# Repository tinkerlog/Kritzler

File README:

==============
 Der Kritzler
==============

 Der Kritzler is a software and hardware platform for developing wall plotters. 
 It consists of a set of Processing sketches (see src/ folder), Arduino firmware 
 (firmware/ folder) and some electronics (some files in the design/ folder). 

 More can be found here:
 http://tinkerlog.com/2011/09/02/der-kritzler/
 
 If you want me to pull your changes, please consider:
 * Use spaces, no tabs.
 * Indention: 2 spaces.

 src/ 
      Contains Processing/Java sources, ready to use in Eclipse.
      Take a look at http://processing.org/learning/eclipse/
      to see how to set things up.
      
 firmware/
      Contains Arduino firmware for the Kritzler.

 jpg_to_svg_bw.sh
      Script to convert a bitmap into an SVG.
      Needs imagemagick and potrace.
    
 jpg_to_svg.sh
      Starts the processing sketch to make a jittered SVG
      out of a bitmap (JPG).
      
 fill_svg.sh 
      Starts the processing sketch to fill SVG outlines with
      with diagonal lines.
      
 plotter.sh
      Starts the processing sketch that sends SVGs to the Kritzler.

===========
 Changelog
===========
 + Added controlP5 menus and buttons to the Plotter UI.
 + Added real-time pen location tracking - Jason Webb (5/25/2012)
 + Added Javadoc comments and consistent formatting added by - Jason Webb (5/25/2012)
 + Added ability to navigate through all SVG files in BUFFER_ACC folder using [ (back) and ] (forward) - Jason Webb (5/31/2012)
 + Added toggle-able grid to canvas, for accurate positioning (toggle with 'g') - Jason Webb (6/1/2012)
 + Added toggle-able bounding box for SVG shape, with centroid markings, for accurate positioning (toggle with 'b') - Jason Webb (6/1/2012)
 + Background color (canvas border) now changes to reflect state of pen plotter (same color as pen location marker). - Jason Webb (6/3/2012)

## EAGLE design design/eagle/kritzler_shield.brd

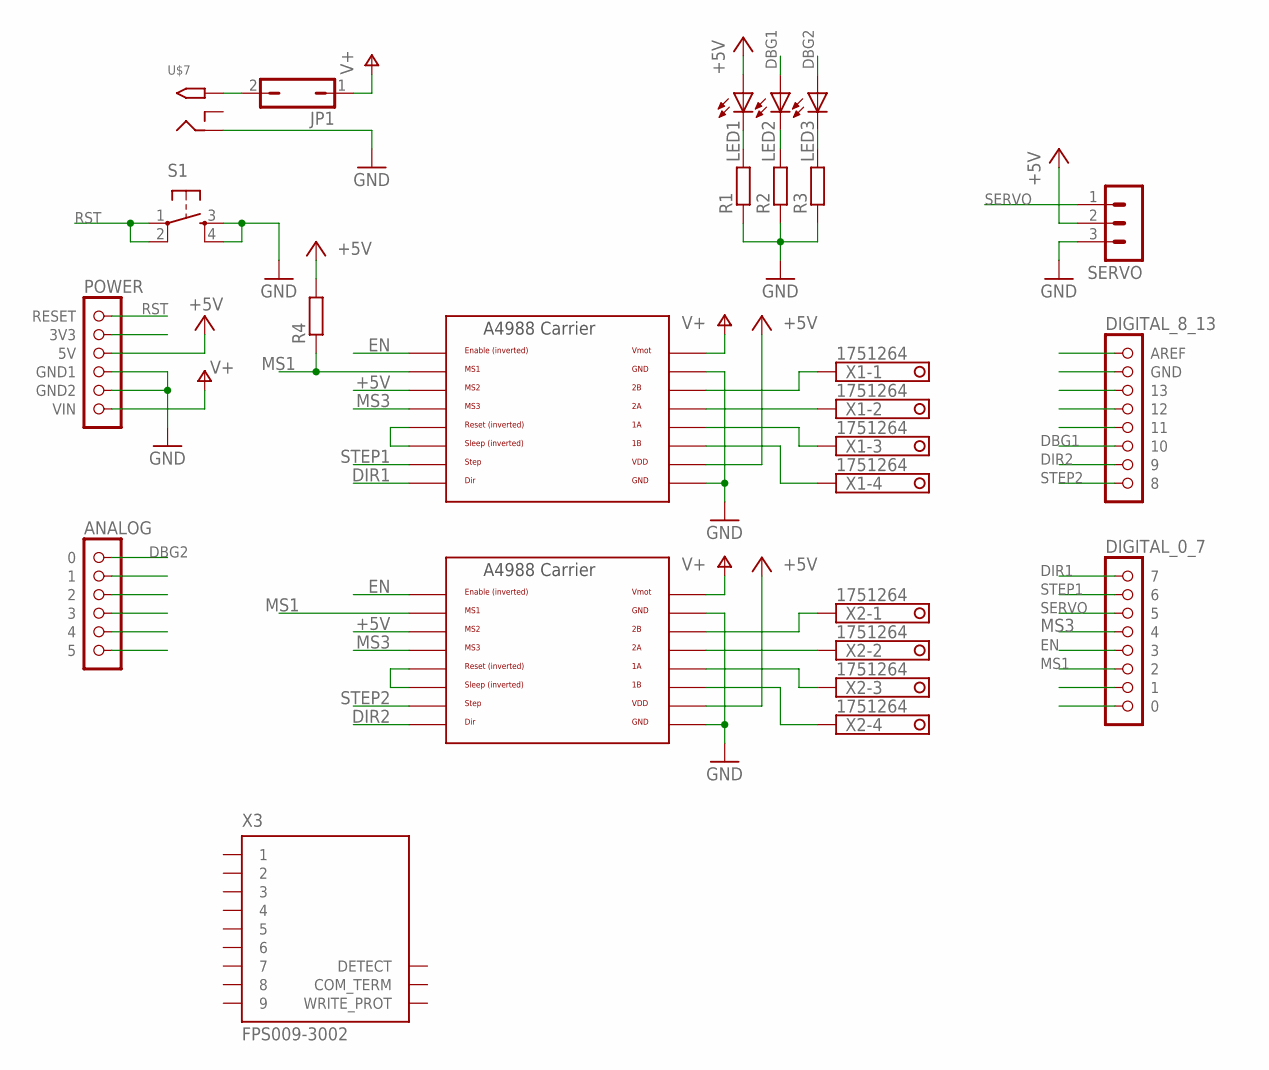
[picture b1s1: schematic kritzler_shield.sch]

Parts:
JP1: JP1Q; JP1
LED1, LED2, LED3: LED5MM
R1, R2, R3, R4: R-EU_0207/10; 0207/10
S1: TAC_SWITCHPTH; TACTILE-PTH
SERVO: MA03-1
U$1: POWER; 1X06
U$2: ANALOG; 1X06
U$3: DIGITAL_0_7; 1X08
U$4: DIGITAL_8_13; 1X08
U$5, U$6: A4988BREAKOUT
U$7: 2.1MMJACKTHM; PJ-102A
X1, X2: 1751264
X3: FPS009-3002; FPS009-3000

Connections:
+5V: LED1.A, R4.2, SERVO.2, U$1.3 (5V), U$5.MS2, U$5.VDD, U$6.MS2, U$6.VDD
DBG1: LED2.A, U$4.6 (10)
DBG2: LED3.A, U$2.1 (0)
DIR1: U$3.1 (7), U$5.DIR
DIR2: U$4.7 (9), U$6.DIR
EN: U$3.5 (3), U$5.EN, U$6.EN
GND: R1.1, R2.1, R3.1, S1.3, S1.4, SERVO.3, U$1.4 (GND1), U$1.5 (GND2), U$5.GND, U$5.GND@0 (GND), U$6.GND, U$6.GND@0 (GND), U$7.RING
MS1: R4.1, U$3.6 (2), U$5.MS1, U$6.MS1
MS3: U$3.4, U$5.MS3, U$6.MS3
unnamed: JP1.2, U$7.TIP
unnamed: LED1.K (C), R1.2
unnamed: LED2.K (C), R2.2
unnamed: LED3.K (C), R3.2
unnamed: U$5.2A, X1.2
unnamed: U$5.1A, X1.3
unnamed: U$5.1B, X1.4
unnamed: U$5.2B, X1.1
unnamed: U$6.2A, X2.2
unnamed: U$6.2B, X2.1
unnamed: U$6.1A, X2.3
unnamed: U$6.1B, X2.4
unnamed: U$6.RST, U$6.SLP (SLEEP)
unnamed: U$5.RST, U$5.SLP (SLEEP)
RST: S1.1, S1.2, U$1.1 (RESET)
SERVO: SERVO.1, U$3.3 (5)
STEP1: U$3.2 (6), U$5.STEP
STEP2: U$4.8, U$6.STEP
T1: U$3.8 (0)
T2: U$3.7 (1)
V+: JP1.1, U$1.6 (VIN), U$5.VMOT, U$6.VMOT
X2: U$4.5 (11)
X3: U$4.4 (12)

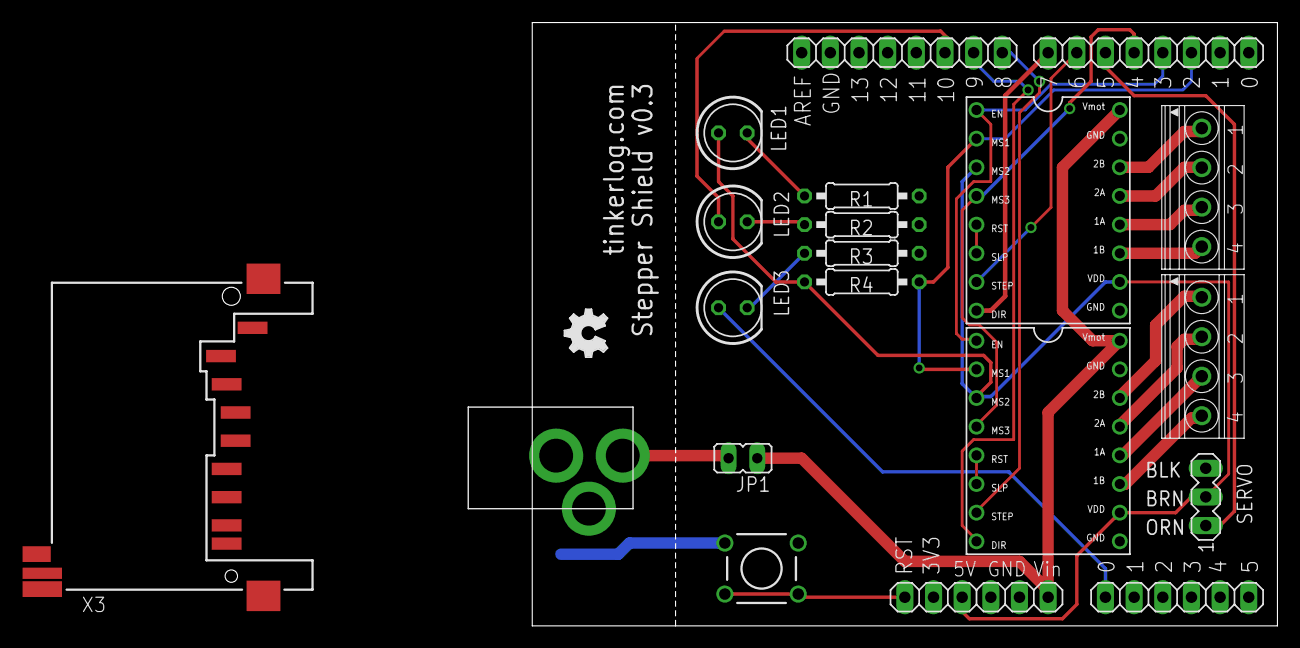
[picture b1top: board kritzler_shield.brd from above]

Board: 2 copper layers, 66.0 x 53.5 mm, 21 parts (0 on the bottom side), 28 nets.

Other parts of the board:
U$8: OSHW_FILLX150_NOTEXT

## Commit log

2011-09-02 first
2011-09-02 initial
2011-09-02 missing design for the laser cutter
2012-03-09 new design files
2012-03-09 new firmware for the upcomming shield
2012-04-05 wiring fixed
2012-04-05 adapt to new firmware
2012-04-05 new firmware
2012-04-16 some changes to the protocol
2012-04-16 removed unused parts
2012-05-26 Added real-time pen location tracking and loads of Javadoc comments
2012-05-27 Fixing formatting issues
2012-06-02 Updates to Plotter.java and changelog
2012-06-03 Background color now changes with pen state
2012-06-08 merged
    Conflicts:
    README
    src/com/tinkerlog/kritzler/Kritzler.java
    src/com/tinkerlog/kritzler/Plotter.java
2012-06-08 revert changes on schematics
2012-06-08 added config files
2012-06-13 added some controlP5 menus and buttons
2012-07-03 my screen is too small
2012-07-03 added some optimization to make it work with StippleGen
2012-07-28 added images for wiki
2012-07-28 missing picture
2015-01-31 add Kritz-A-Sketch firmware
